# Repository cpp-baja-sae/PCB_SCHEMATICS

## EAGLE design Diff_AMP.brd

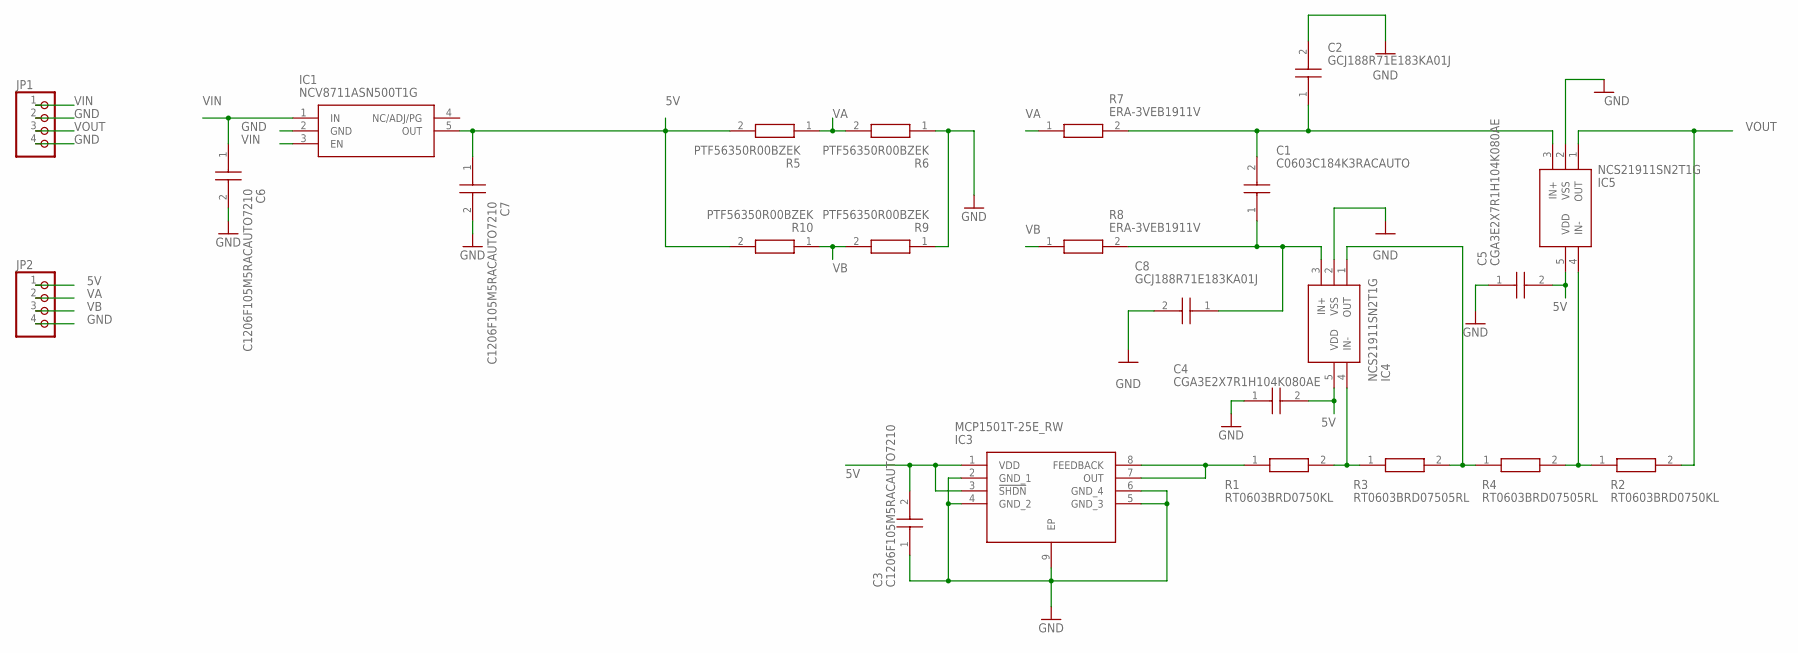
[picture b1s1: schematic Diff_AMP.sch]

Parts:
C1: C0603C184K3RACAUTO; C0603
C2, C8: GCJ188R71E183KA01J; CAPC1608X100N
C3, C6, C7: C1206F105M5RACAUTO7210; C1206
C4, C5: CGA3E2X7R1H104K080AE; CAPC1608X90N
IC1: NCV8711ASN500T1G; SOT95P275X110-5N
IC3: MCP1501T-25E_RW; SON50P200X200X80-9N
IC4, IC5: NCS21911SN2T1G; SOT95P275X110-5N
JP1, JP2: PINHD-1X4; 1X04
R1, R2: RT0603BRD0750KL; RESC1608X55N
R3, R4: RT0603BRD07505RL; RESC1608X55N
R5, R6, R9, R10: PTF56350R00BZEK; RESAD1559W64L635D231
R7, R8: ERA-3VEB1911V; ERA3KV_(0603)

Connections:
5V: C3.2, C4.2, C5.2, C7.1, IC1.5 (OUT), IC3.1 (VDD), IC3.3 (!SHDN), IC4.5 (VDD), IC5.5 (VDD), JP2.1, R5.2, R10.2
GND: C2.2, C3.1, C4.1, C5.1, C6.2, C7.2, C8.2, IC1.2 (GND), IC3.2 (GND_1), IC3.4 (GND_2), IC3.5 (GND_3), IC3.6 (GND_4), IC3.9 (EP), IC4.2 (VSS), IC5.2 (VSS), JP1.2, JP1.4, JP2.4, R6.1, R9.1
unnamed: IC3.7 (OUT), IC3.8 (FEEDBACK), R1.1
unnamed: IC4.4 (IN-), R1.2, R3.1
unnamed: C1.1, C8.1, IC4.3 (IN+), R8.2
unnamed: C1.2, C2.1, IC5.3 (IN+), R7.2
unnamed: IC4.1 (OUT), R3.2, R4.1
unnamed: IC5.4 (IN-), R2.1, R4.2
VA: JP2.2, R5.1, R6.2, R7.1
VB: JP2.3, R8.1, R9.2, R10.1
VIN: C6.1, IC1.1 (IN), IC1.3 (EN), JP1.1
VOUT: IC5.1 (OUT), JP1.3, R2.2

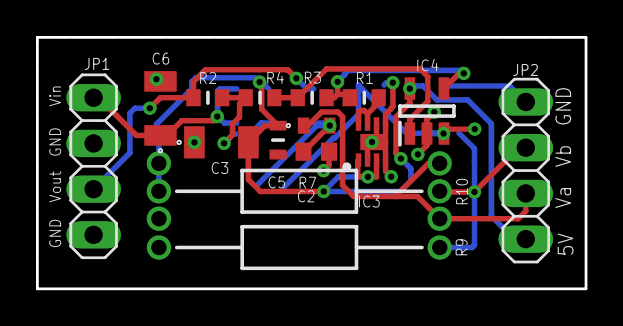
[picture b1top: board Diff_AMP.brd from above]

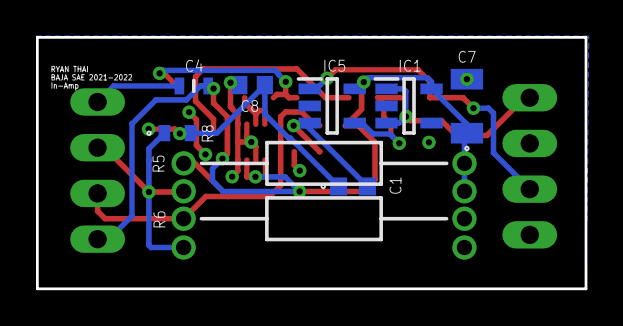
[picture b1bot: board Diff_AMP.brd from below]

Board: 2 copper layers, 30.5 x 14.0 mm, 24 parts (9 on the bottom side), 12 nets.

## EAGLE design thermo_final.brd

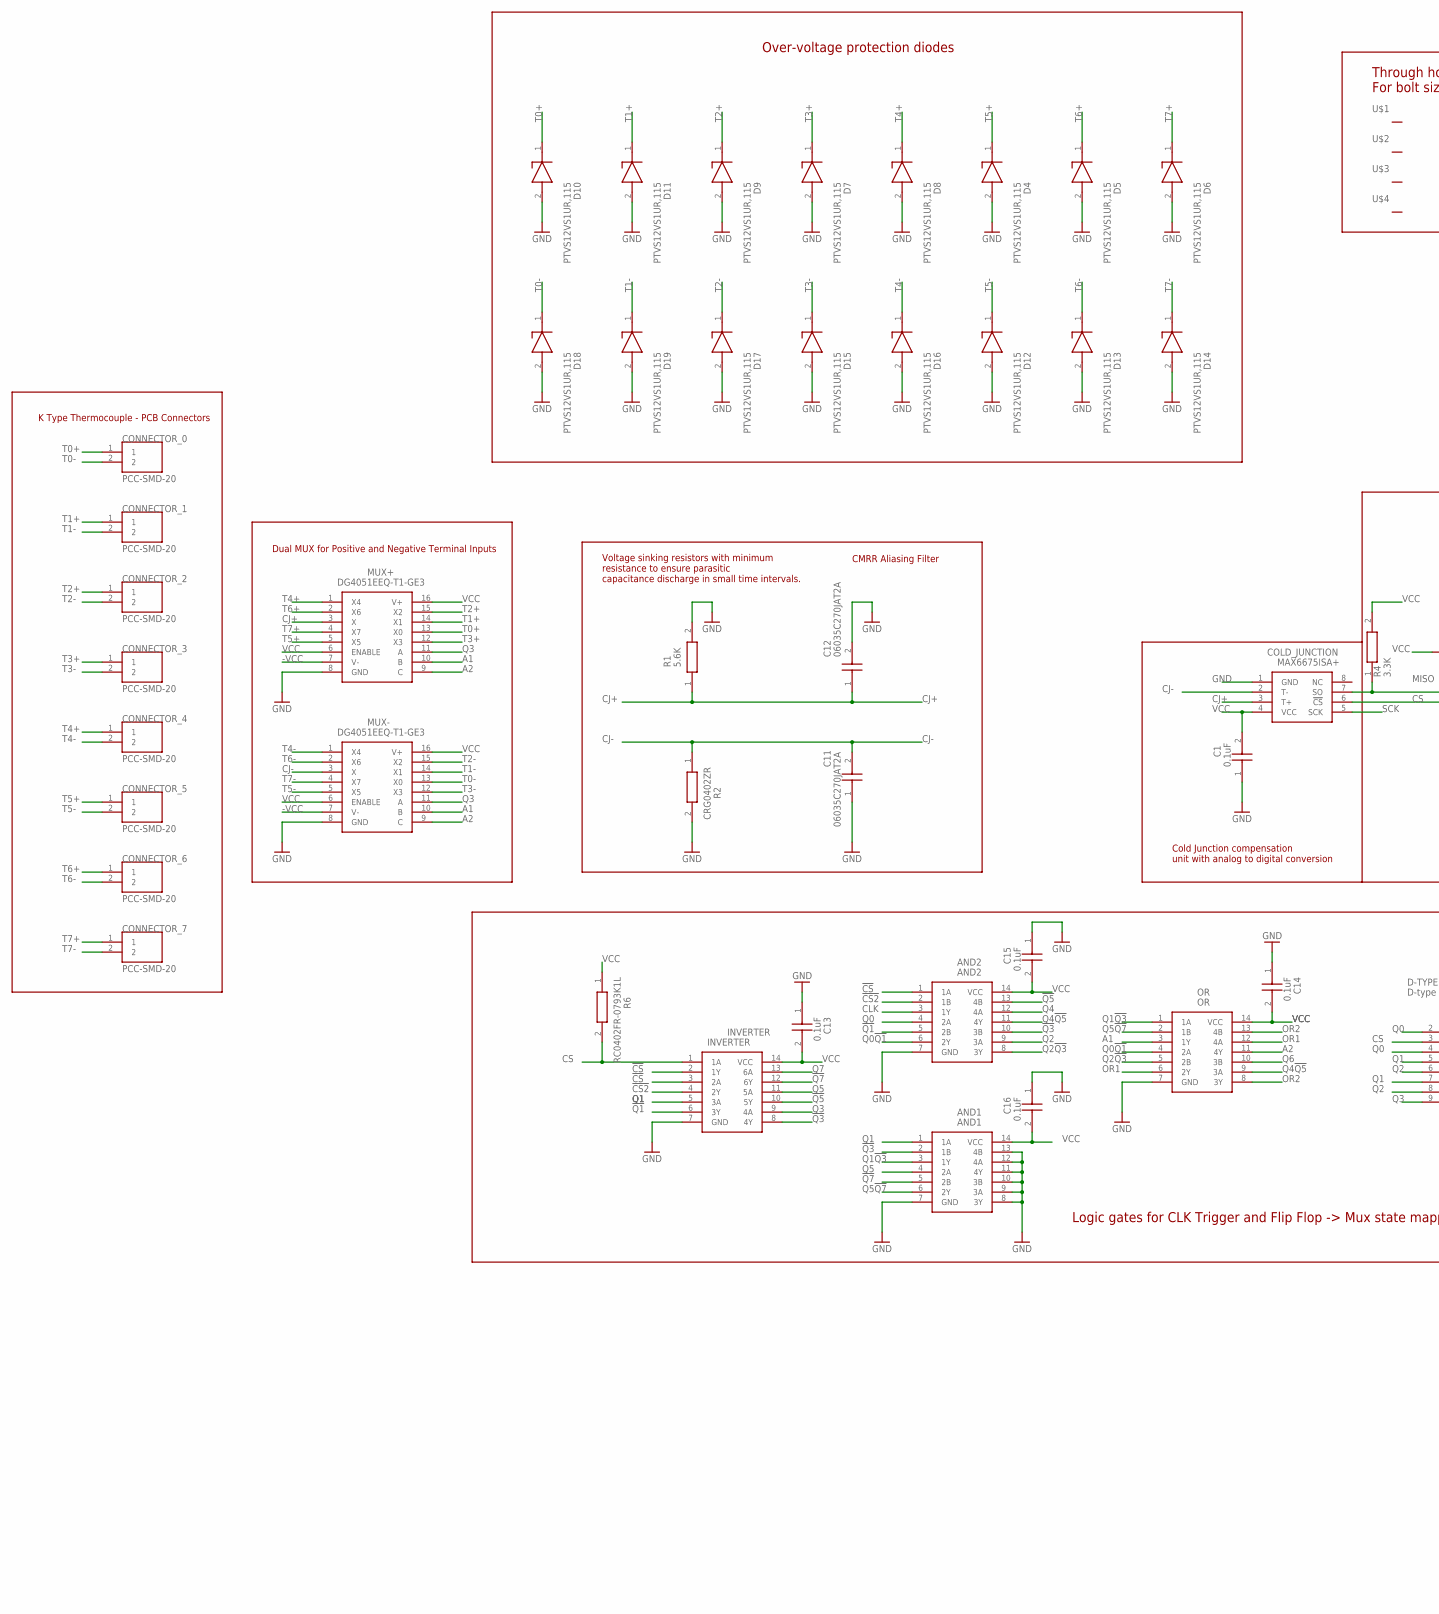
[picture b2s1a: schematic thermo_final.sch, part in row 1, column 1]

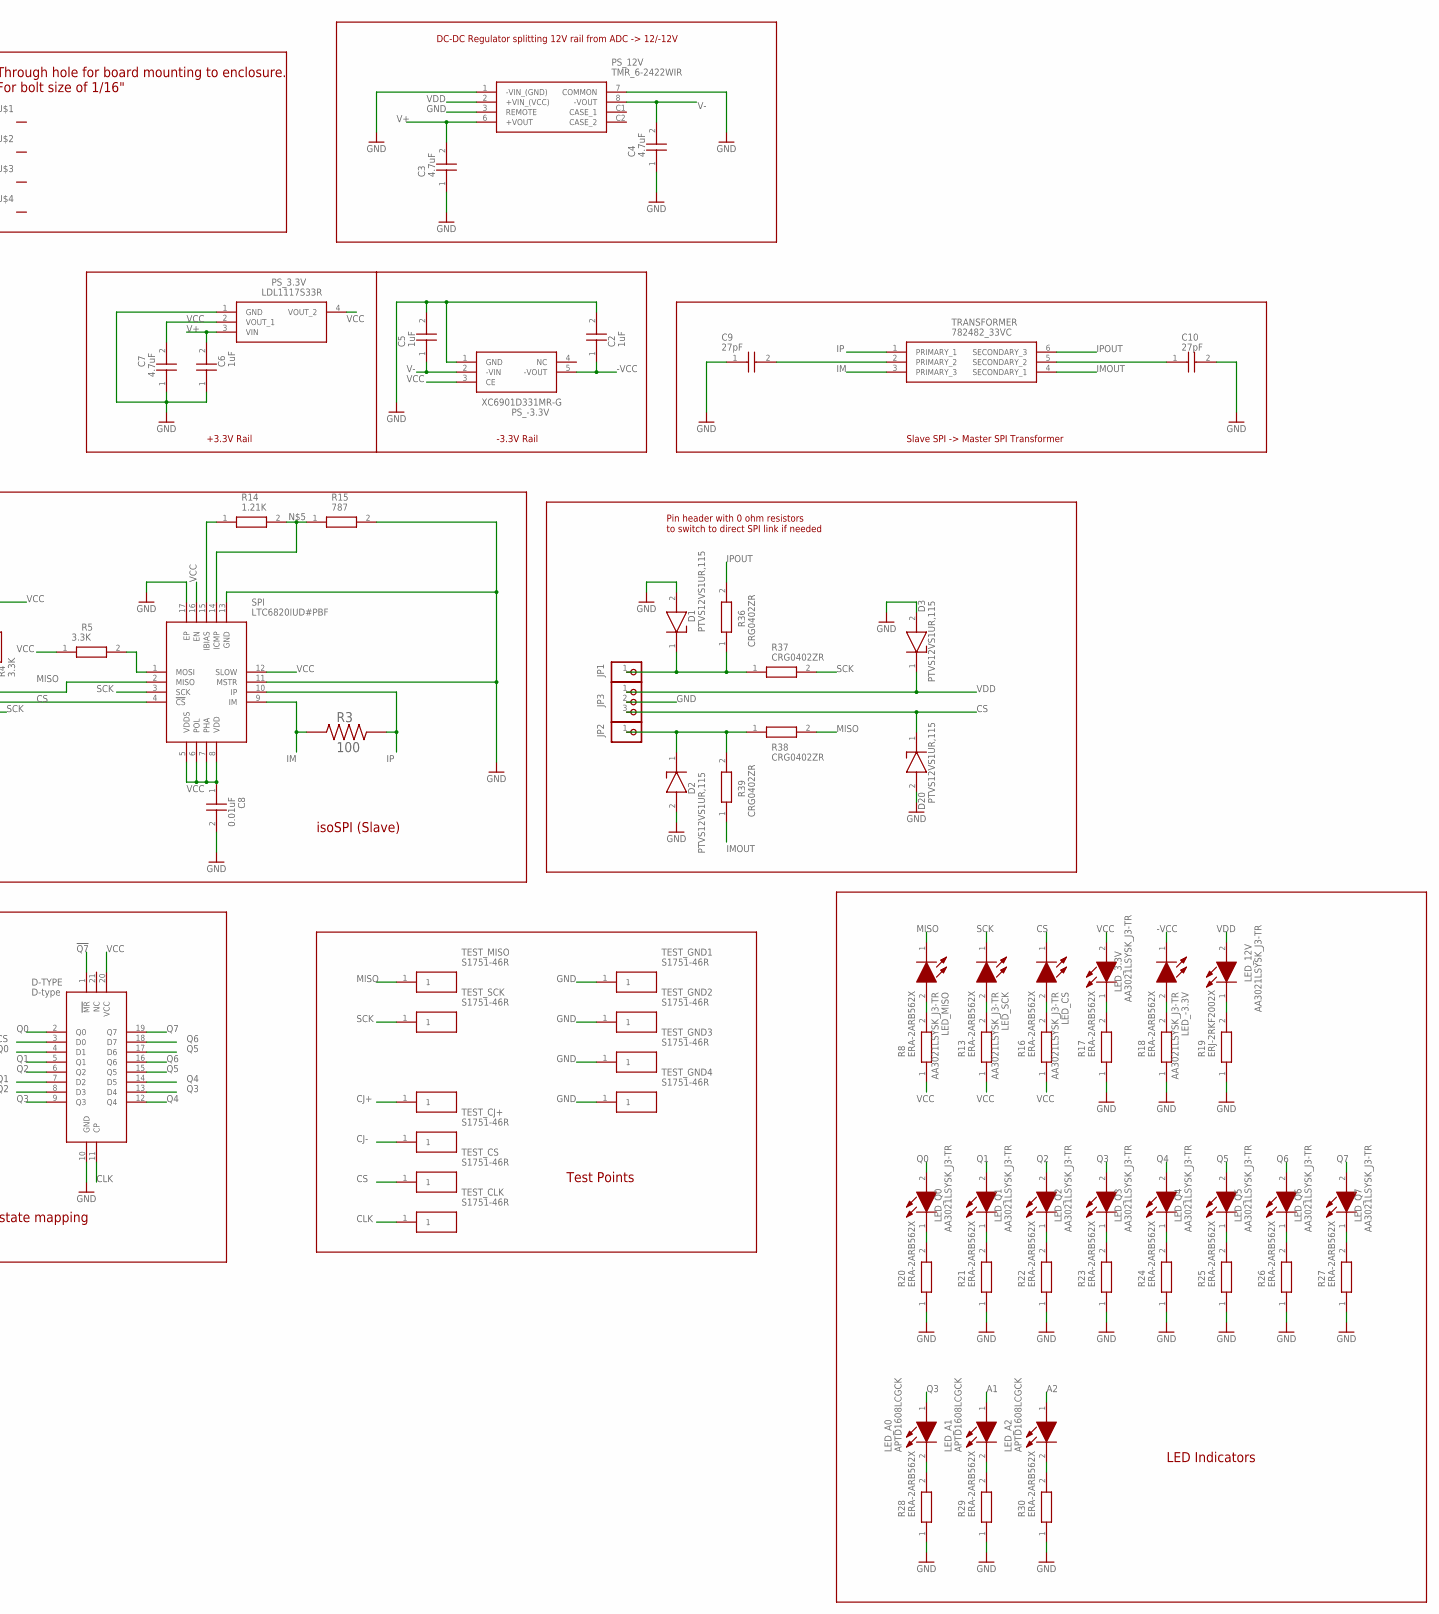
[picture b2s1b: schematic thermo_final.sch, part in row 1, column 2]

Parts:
AND1: AND1; SOIC127P600X175-14N
AND2: AND2; SOIC127P600X175-14N
C1, C13, C14, C15, C16: 0.1uF; CAPC1608X90N
C2, C5, C6: 1uF; CAPC1608X90N
C3, C4, C7: 4.7uF; CAPC1608X90N
C8: 0.01uF; CAPC1005X55N
C9, C10: 27pF; CAPC1608X90N
C11, C12: 06035C270JAT2A; CAPC1608X90N
COLD_JUNCTION: MAX6675ISA+; SOIC127P600X175-8N
CONNECTOR_0, CONNECTOR_1, CONNECTOR_2, CONNECTOR_3, CONNECTOR_4, CONNECTOR_5, CONNECTOR_6, CONNECTOR_7: PCC-SMD-20; OMEGA_PCC-SMD-20
D1, D2, D3, D4, D5, D6, D7, D8, D9, D10, D11, D12, D13, D14, D15, D16, D17, D18, D19, D20: PTVS12VS1UR,115; SOD123W
D-TYPE: D-type; QFN50P450X250X100-21N
INVERTER: INVERTER; SOIC127P600X175-14N
JP1, JP2: PINHD-1X1; 1X01
JP3: PINHD-1X3; 1X03
LED_3.3V, LED_12V: AA3021LSYSK_J3-TR; AA3021LSYSKJ3TR
LED_-3.3V: AA3021LSYSK_J3-TR; AA3021LSYSKJ3TR
LED_A0, LED_A1, LED_A2: APTD1608LCGCK; APT1608CGCK
LED_CS: AA3021LSYSK_J3-TR; AA3021LSYSKJ3TR
LED_MISO: AA3021LSYSK_J3-TR; AA3021LSYSKJ3TR
LED_Q0, LED_Q1, LED_Q2, LED_Q3, LED_Q4, LED_Q5, LED_Q6, LED_Q7: AA3021LSYSK_J3-TR; AA3021LSYSKJ3TR
LED_SCK: AA3021LSYSK_J3-TR; AA3021LSYSKJ3TR
MUX+: DG4051EEQ-T1-GE3; SOP65P640X120-16N
MUX-: DG4051EEQ-T1-GE3; SOP65P640X120-16N
OR: OR; SOIC127P600X175-14N
PS_3.3V: LDL1117S33R; SOT230P700X180-4N
PS_12V: TMR_6-2422WIR; TMR67212WIR
PS_-3.3V: XC6901D331MR-G; SOT95P280X130-5N
R1: 5.6K; ERA2AED122X
R2, R36, R37, R38, R39: CRG0402ZR; RESC1005X40N
R3: 100; RESC1005X40N
R4, R5: 3.3K; RESC1005X40N
R6: RC0402FR-0793K1L; RESC1005X40N
R8, R13, R16, R17, R18, R20, R21, R22, R23, R24, R25, R26, R27, R28, R29, R30: ERA-2ARB562X; ERA2AED122X
R14: 1.21K; RESC1005X35N
R15: 787; ERA2AED122X
R19: ERJ-2RKF2002X; ERJ2R_(0402)
SPI: LTC6820IUD#PBF; QFN50P300X300X80-17N
TEST_CJ+: S1751-46R; S175146R
TEST_CJ-: S1751-46R; S175146R
TEST_CLK: S1751-46R; S175146R
TEST_CS: S1751-46R; S175146R
TEST_GND1, TEST_GND2, TEST_GND3, TEST_GND4: S1751-46R; S175146R
TEST_MISO: S1751-46R; S175146R
TEST_SCK: S1751-46R; S175146R
TRANSFORMER: 782482_33VC; DIP1016W60P254L914H635Q6N
U$1, U$2, U$3, U$4: THROUGH_HOLE

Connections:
!CS: AND2.1 (1A), INVERTER.2 (1Y), INVERTER.3 (2A)
!CS2: AND2.2 (1B), INVERTER.4 (2Y)
!Q1: AND2.5 (2B), INVERTER.6 (3Y)
!Q3: AND1.2 (1B), AND2.10 (3B), INVERTER.8 (4Y)
!Q5: AND2.13 (4B), INVERTER.10 (5Y)
!Q7: AND1.5 (2B), D-TYPE.1 (!MR), INVERTER.12 (6Y)
-VCC: C2.1, LED_-3.3V.1 (K), MUX+.7 (V-), MUX-.7 (V-), PS_-3.3V.5 (-VOUT)
A1: LED_A1.1 (A), MUX+.10 (B), MUX-.10 (B), OR.3 (1Y)
A2: LED_A2.1 (A), MUX+.9 (C), MUX-.9 (C), OR.11 (4Y)
CJ+: C12.1, COLD_JUNCTION.3 (T+), MUX+.3 (X), R1.1, TEST_CJ-.1
CJ-: C11.2, COLD_JUNCTION.2 (T-), MUX-.3 (X), R2.1, TEST_CJ+.1
CLK: AND2.3 (1Y), D-TYPE.11 (CP), TEST_CLK.1
CS: COLD_JUNCTION.6 (!CS), D20.1 (K), D-TYPE.3 (D0), INVERTER.1 (1A), JP3.3, LED_CS.1 (K), R6.2, SPI.4 (!CS), TEST_CS.1
GND: AND1.7 (GND), AND1.8 (3Y), AND1.9 (3A), AND1.10 (3B), AND1.11 (4Y), AND1.12 (4A), AND1.13 (4B), AND2.7 (GND), C1.1, C2.2, C3.1, C4.1, C5.2, C6.1, C7.1, C8.2, C9.1, C10.2, C11.1, C12.2, C13.1, C14.1, C15.1, C16.1, COLD_JUNCTION.1 (GND), D1.2 (A), D2.2 (A), D3.2 (A), D4.2 (A), D5.2 (A), D6.2 (A), D7.2 (A), D8.2 (A), D9.2 (A), D10.2 (A), D11.2 (A), D12.2 (A), D13.2 (A), D14.2 (A), D15.2 (A), D16.2 (A), D17.2 (A), D18.2 (A), D19.2 (A), D20.2 (A), D-TYPE.10 (GND), INVERTER.7 (GND), JP3.2, MUX+.8 (GND), MUX-.8 (GND), OR.7 (GND), PS_3.3V.1 (GND), PS_12V.1 (-VIN_(GND)), PS_12V.3 (REMOTE), PS_12V.7 (COMMON), PS_-3.3V.1 (GND), R1.2, R2.2, R15.2, R17.1, R18.1, R19.1, R20.1, R21.1, R22.1, R23.1, R24.1, R25.1, R26.1, R27.1, R28.1, R29.1, R30.1, SPI.11 (MSTR), SPI.13 (GND), SPI.17 (EP), TEST_GND1.1, TEST_GND2.1, TEST_GND3.1, TEST_GND4.1
IM: R3.1, SPI.9 (IM), TRANSFORMER.3 (PRIMARY_3)
IMOUT: R39.1, TRANSFORMER.4 (SECONDARY_1)
IP: R3.2, SPI.10 (IP), TRANSFORMER.1 (PRIMARY_1)
IPOUT: R36.2, TRANSFORMER.6 (SECONDARY_3)
MISO: COLD_JUNCTION.7 (SO), LED_MISO.1 (K), R4.1, R38.2, SPI.2 (MISO), TEST_MISO.1
unnamed: LED_12V.1 (K), R19.2
unnamed: R14.2, R15.1, SPI.14 (ICMP)
unnamed: LED_Q0.1 (K), R20.2
unnamed: C9.2, TRANSFORMER.2 (PRIMARY_2)
unnamed: R14.1, SPI.15 (IBIAS)
unnamed: LED_Q1.1 (K), R21.2
unnamed: C10.1, TRANSFORMER.5 (SECONDARY_2)
unnamed: LED_Q2.1 (K), R22.2
unnamed: LED_Q3.1 (K), R23.2
unnamed: LED_MISO.2 (A), R8.2
unnamed: R5.2, SPI.1 (MOSI)
unnamed: LED_SCK.2 (A), R13.2
unnamed: LED_CS.2 (A), R16.2
unnamed: LED_3.3V.1 (K), R17.2
unnamed: LED_-3.3V.2 (A), R18.2
unnamed: LED_Q4.1 (K), R24.2
unnamed: LED_Q5.1 (K), R25.2
unnamed: LED_Q6.1 (K), R26.2
unnamed: LED_Q7.1 (K), R27.2
unnamed: LED_A0.2 (K), R28.2
unnamed: LED_A1.2 (K), R29.2
unnamed: LED_A2.2 (K), R30.2
unnamed: D1.1 (K), JP1.1, R36.1, R37.1
unnamed: D2.1 (K), JP2.1, R38.1, R39.2
OR1: OR.6 (2Y), OR.12 (4A)
OR2: OR.8 (3Y), OR.13 (4B)
Q0: AND2.4 (2A), D-TYPE.2 (Q0), D-TYPE.4 (D1), LED_Q0.2 (A)
Q0!Q1: AND2.6 (2Y), OR.4 (2A)
Q1: AND1.1 (1A), D-TYPE.5 (Q1), D-TYPE.7 (D2), INVERTER.5 (3A), LED_Q1.2 (A)
Q1!Q3: AND1.3 (1Y), OR.1 (1A)
Q2: AND2.9 (3A), D-TYPE.6 (Q2), D-TYPE.8 (D3), LED_Q2.2 (A)
Q2!Q3: AND2.8 (3Y), OR.5 (2B)
Q3: D-TYPE.9 (Q3), D-TYPE.13 (D4), INVERTER.9 (4A), LED_A0.1 (A), LED_Q3.2 (A), MUX+.11 (A), MUX-.11 (A)
Q4: AND2.12 (4A), D-TYPE.12 (Q4), D-TYPE.14 (D5), LED_Q4.2 (A)
Q4!Q5: AND2.11 (4Y), OR.9 (3A)
Q5: AND1.4 (2A), D-TYPE.15 (Q5), D-TYPE.17 (D6), INVERTER.11 (5A), LED_Q5.2 (A)
Q5!Q7: AND1.6 (2Y), OR.2 (1B)
Q6: D-TYPE.16 (Q6), D-TYPE.18 (D7), LED_Q6.2 (A), OR.10 (3B)
Q7: D-TYPE.19 (Q7), INVERTER.13 (6A), LED_Q7.2 (A)
SCK: COLD_JUNCTION.5 (SCK), LED_SCK.1 (K), R37.2, SPI.3 (SCK), TEST_SCK.1
T0+: CONNECTOR_0.1, D10.1 (K), MUX+.13 (X0)
T0-: CONNECTOR_0.2, D18.1 (K), MUX-.13 (X0)
T1+: CONNECTOR_1.1, D11.1 (K), MUX+.14 (X1)
T1-: CONNECTOR_1.2, D19.1 (K), MUX-.14 (X1)
T2+: CONNECTOR_2.1, D9.1 (K), MUX+.15 (X2)
T2-: CONNECTOR_2.2, D17.1 (K), MUX-.15 (X2)
T3+: CONNECTOR_3.1, D7.1 (K), MUX+.12 (X3)
T3-: CONNECTOR_3.2, D15.1 (K), MUX-.12 (X3)
T4+: CONNECTOR_4.1, D8.1 (K), MUX+.1 (X4)
T4-: CONNECTOR_4.2, D16.1 (K), MUX-.1 (X4)
T5+: CONNECTOR_5.1, D4.1 (K), MUX+.5 (X5)
T5-: CONNECTOR_5.2, D12.1 (K), MUX-.5 (X5)
T6+: CONNECTOR_6.1, D5.1 (K), MUX+.2 (X6)
T6-: CONNECTOR_6.2, D13.1 (K), MUX-.2 (X6)
T7+: CONNECTOR_7.1, D6.1 (K), MUX+.4 (X7)
T7-: CONNECTOR_7.2, D14.1 (K), MUX-.4 (X7)
V+: C3.2, C6.2, PS_3.3V.3 (VIN), PS_12V.6 (+VOUT)
V-: C4.2, C5.1, PS_12V.8 (-VOUT), PS_-3.3V.2 (-VIN)
VCC: AND1.14 (VCC), AND2.14 (VCC), C1.2, C7.2, C8.1, C13.2, C14.2, C15.2, C16.2, COLD_JUNCTION.4 (VCC), D-TYPE.20 (VCC), INVERTER.14 (VCC), LED_3.3V.2 (A), MUX+.6 (ENABLE), MUX+.16 (V+), MUX-.6 (ENABLE), MUX-.16 (V+), OR.14 (VCC), PS_3.3V.2 (VOUT_1), PS_3.3V.4 (VOUT_2), PS_-3.3V.3 (CE), R4.2, R5.1, R6.1, R8.1, R13.1, R16.1, SPI.5 (VDDS), SPI.6 (POL), SPI.7 (PHA), SPI.8 (VDD), SPI.12 (SLOW), SPI.16 (EN)
VDD: D3.1 (K), JP3.1, LED_12V.2 (A), PS_12V.2 (+VIN_(VCC))

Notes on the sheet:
DC-DC Regulator splitting 12V rail from ADC -> 12/-12V
Over-voltage protection diodes
K Type Thermocouple - PCB Connectors
+3.3V Rail
-3.3V Rail
Slave SPI -> Master SPI Transformer
Logic gates for CLK Trigger and Flip Flop -> Mux state mapping
LED Indicators
Test Points
Dual MUX for Positive and Negative Terminal Inputs
Voltage sinking resistors with minimum resistance to ensure parasitic capacitance discharge in small time intervals.
Pin header with 0 ohm resistors to switch to direct SPI link if needed
Cold Junction compensation unit with analog to digital conversion
isoSPI (Slave)
Through hole for board mounting to enclosure. For bolt size of 1/16"
CMRR Aliasing Filter

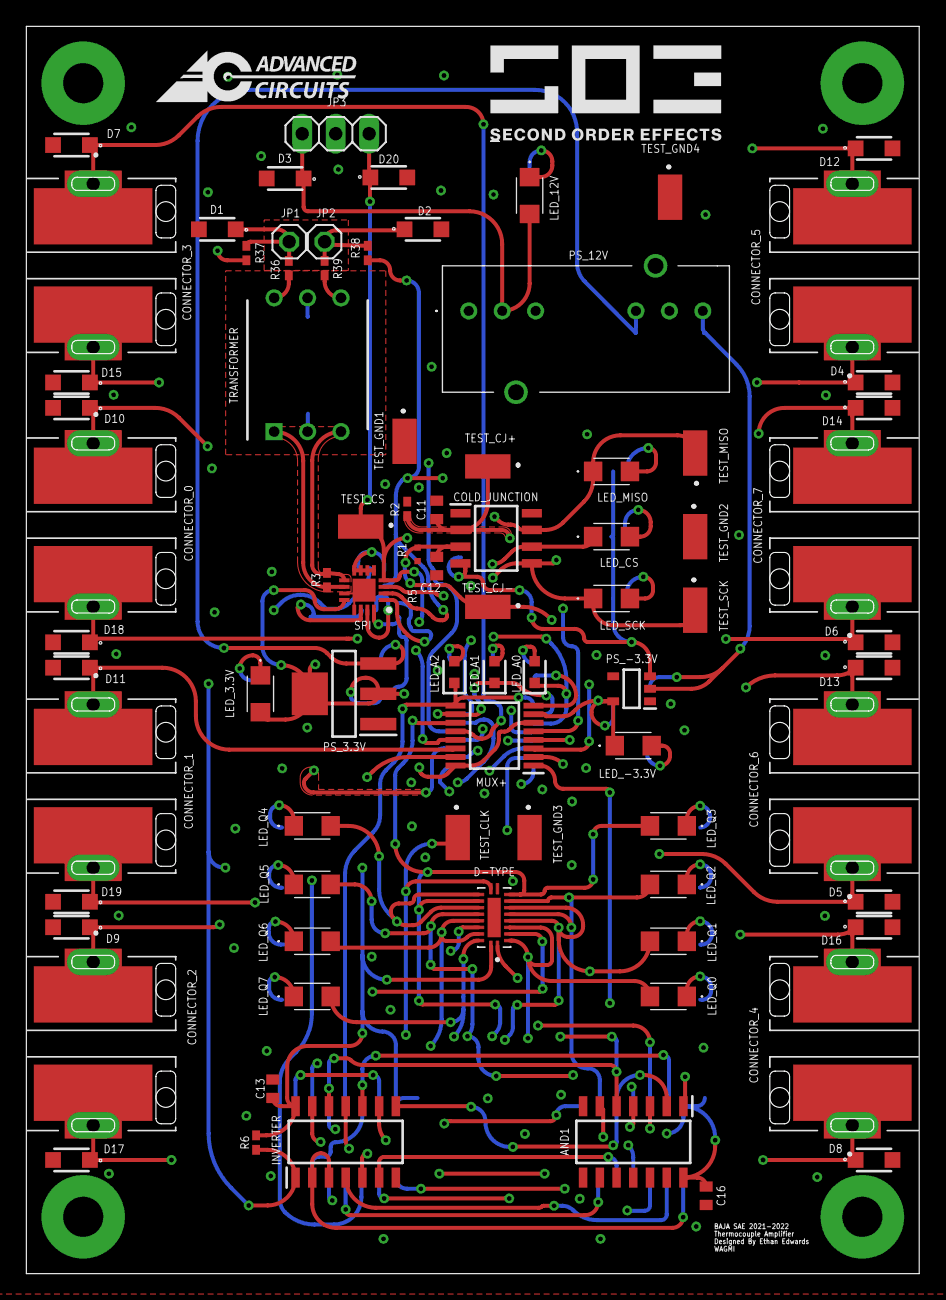
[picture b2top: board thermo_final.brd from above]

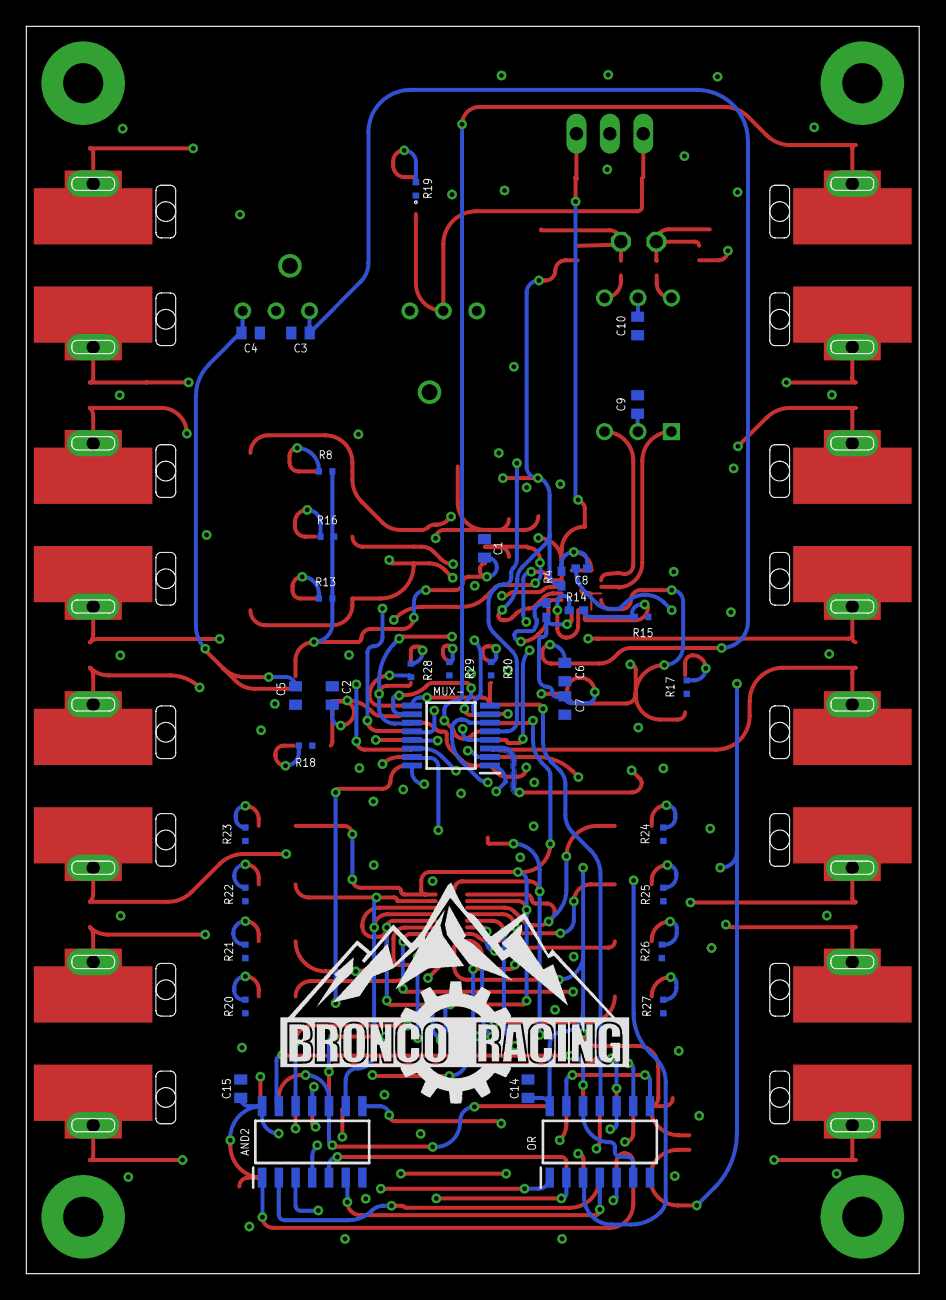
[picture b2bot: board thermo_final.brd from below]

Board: 4 copper layers, 67.8 x 94.7 mm, 120 parts (36 on the bottom side), 79 nets.
